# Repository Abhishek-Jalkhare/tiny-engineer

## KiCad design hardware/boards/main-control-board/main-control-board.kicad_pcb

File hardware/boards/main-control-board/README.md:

# main-control-board

This board drives the robot's servos and speaker. Power and USB data come in on a USB-C connector. The Waveshare ESP32-C3-Zero is not soldered down; it plugs into two 9-pin sockets.

- **Status:** draft (schematic and routed layout)
- **KiCad:** 10
- **Built:** not manufactured
- **Tested:** not tested

## Soldered on the board

The servo driver, the speaker amplifier, and the USB-C connector are parts on this PCB. They replace the plug-in PCA9685 board, the MAX98357A breakout, and the Adafruit 5993 USB-C breakout.

- **PCA9685** drives up to 16 PWM channels. This robot uses five of them for the servos. The I2C address is `0x40`: the address pins and the external-clock pin are tied to ground, so the chip uses its own clock.
- **Servo header** takes five servo plugs. Each plug has ground, 5 V, and a PWM signal.
- **MAX98357A** is the mono class-D amplifier. The speaker connects to a 2-pin header. The speaker's minus terminal is not ground. Connect the speaker only between the two amplifier outputs.
- **USB-C connector** supplies 5 V and the USB data pair. Two 5.1 kΩ resistors on the CC pins mark this board as a USB device. The charger decides how much current is available.
- A **3 A resettable fuse** sits between USB power and the 5 V rail.
- A **TPS259571** eFuse (`U4`) sits between that 5 V rail and servo 5 V. Current limit is set by `R14` (1 kΩ ≈ 2 A). On fault the device auto-retries.
- **OLED header** is for the SSD1306 display. Pin order, from pin 1: 3.3 V, ground, SDA, SCL.
- A second header shares that I2C bus. Its pin order is different: ground, 3.3 V, SDA, SCL.
- A **12-pin extension port** (`J4`) breaks out `SERVO_5V`, two grounds, `+3.3V`, I2S BCLK/LRC, and GPIOs GP6–GP9 / GP20 / GP21.
  - GP8 and GP9 are ESP32-C3 strapping pins. Do not pull them low at reset; GP9 low enters download mode.
  - GP20 and GP21 are the default UART0 RX/TX. Boot log output appears on GP21 at power-up.

A solder jumper next to the amplifier is marked as a 6 dB gain limit.

## What still plugs in

The **Waveshare ESP32-C3-Zero** plugs into two 9-pin sockets, one for each row of pins on the module. This board has no ESP32 chip of its own.

The OLED module plugs into the OLED header.

## Power

USB-C 5 V goes through the fuse onto the `+5V` rail. That rail feeds the ESP32 5 V pin, a 5 V indicator LED, and the eFuse input.

The eFuse output is `SERVO_5V`. That rail feeds the servo plugs (PCA9685 V+), a bulk capacitor, and — through a net tie — the amplifier 5 V net, so the amp supply can still be routed on its own but comes from the protected servo rail, not raw `+5V`.

3.3 V comes from the regulator on the ESP32 module. This board does not have a 3.3 V regulator. 3.3 V feeds the PCA9685 logic supply, the OLED, the I2C pull-ups (4.7 kΩ), the pull-up on the PCA9685 output-enable pin (10 kΩ), and a 3.3 V indicator LED.

Servo 5 V and logic 3.3 V stay separate. They share ground.

Use a **5 V supply of at least 2 A**. Five stalled servos can draw more than a typical USB port provides. Multi-servo stall can also hit the eFuse’s ~2 A limit before the 3 A resettable fuse trips.

## Connections from the ESP32

| Function | ESP32 pin | Goes to |
| --- | --- | --- |
| I2C SDA | GP0 | PCA9685 and OLED |
| I2C SCL | GP1 | PCA9685 and OLED |
| I2S bit clock | GP2 | MAX98357A BCLK |
| I2S word clock | GP3 | MAX98357A LRC |
| I2S data | GP4 | MAX98357A DIN |
| Servo output enable | GP5 | PCA9685 output enable (active low) |
| USB D− | GPIO18 | USB-C |
| USB D+ | GPIO19 | USB-C |

GP5 drives PCA9685 OE (`PCA9685_OE_WIRED` in [`include/pins.h`](../../../include/pins.h)). A 10 kΩ pull-up holds OE high until firmware drives it low after neutral park.

## Board

Two-layer FR4, about 1.6 mm thick.

5 V tracks (`+5V` and `SERVO_5V`) are 1.5 mm wide. 3.3 V tracks are 0.4 mm. The amplifier 5 V net is 0.5 mm. USB data tracks use their own width.

The two ESP32 sockets follow the Waveshare header. Pad 1 is 5 V. Pads count anticlockwise from the module's USB connector. Those numbers are the module's header pads, not the pins of the ESP32-C3 chip.

## Library exceptions

### USB1 3D model (C2765186)

Footprint `USB-C-SMD_TYPE-C-16PIN-2MD-073` loads `USB-C-SMD_TYPE-C-6PIN-2MD-073.{wrl,step}`.

EasyEDA has no separate `…16PIN….wrl` for this LCSC part. Official package `c_para.3DModel` is `USB-C-SMD_TYPE-C-6PIN-2MD-073` (outline3D uuid `4ee8413127e64716b804db03d4b340ae`). Re-import via `import_lcsc.py --lcsc-id C2765186` reproduces the same mapping.

Do not rename or replace the model only to silence filename-mismatch reviews — this is intentional.

Contribution rules: [`docs/pcb.md`](../../../docs/pcb.md).

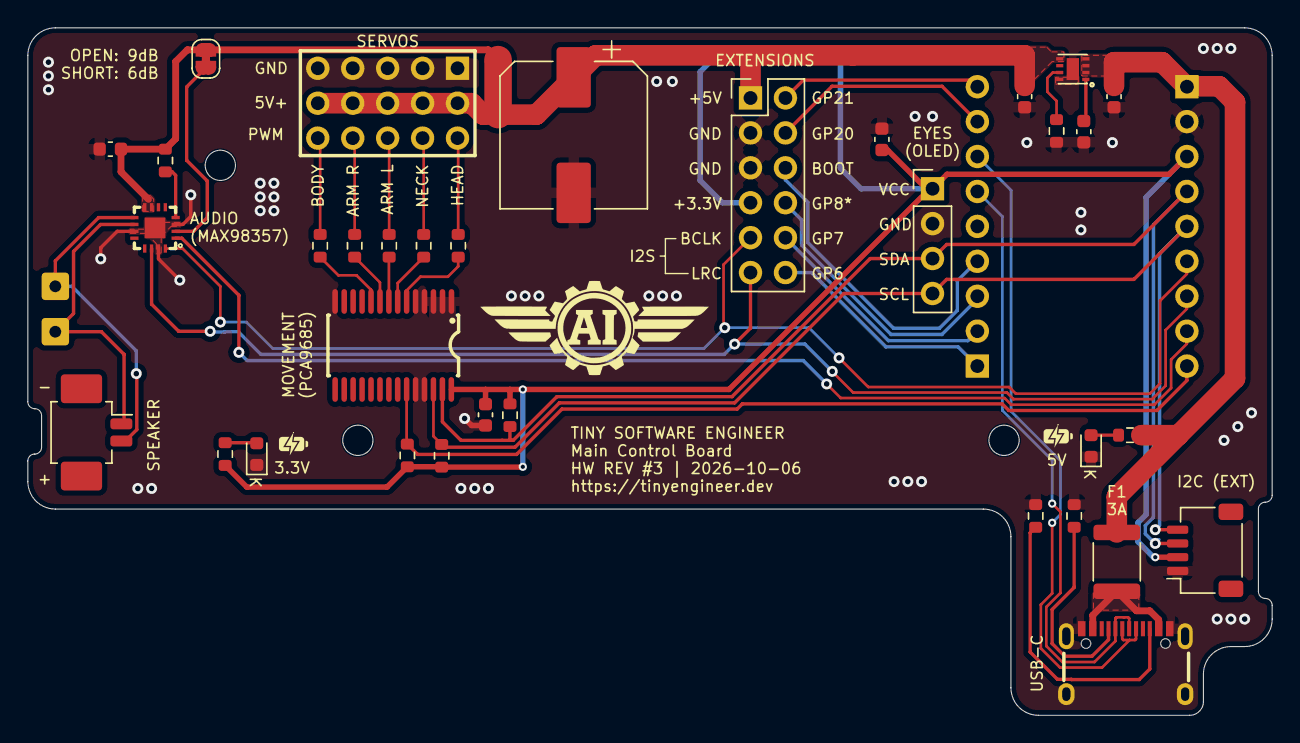
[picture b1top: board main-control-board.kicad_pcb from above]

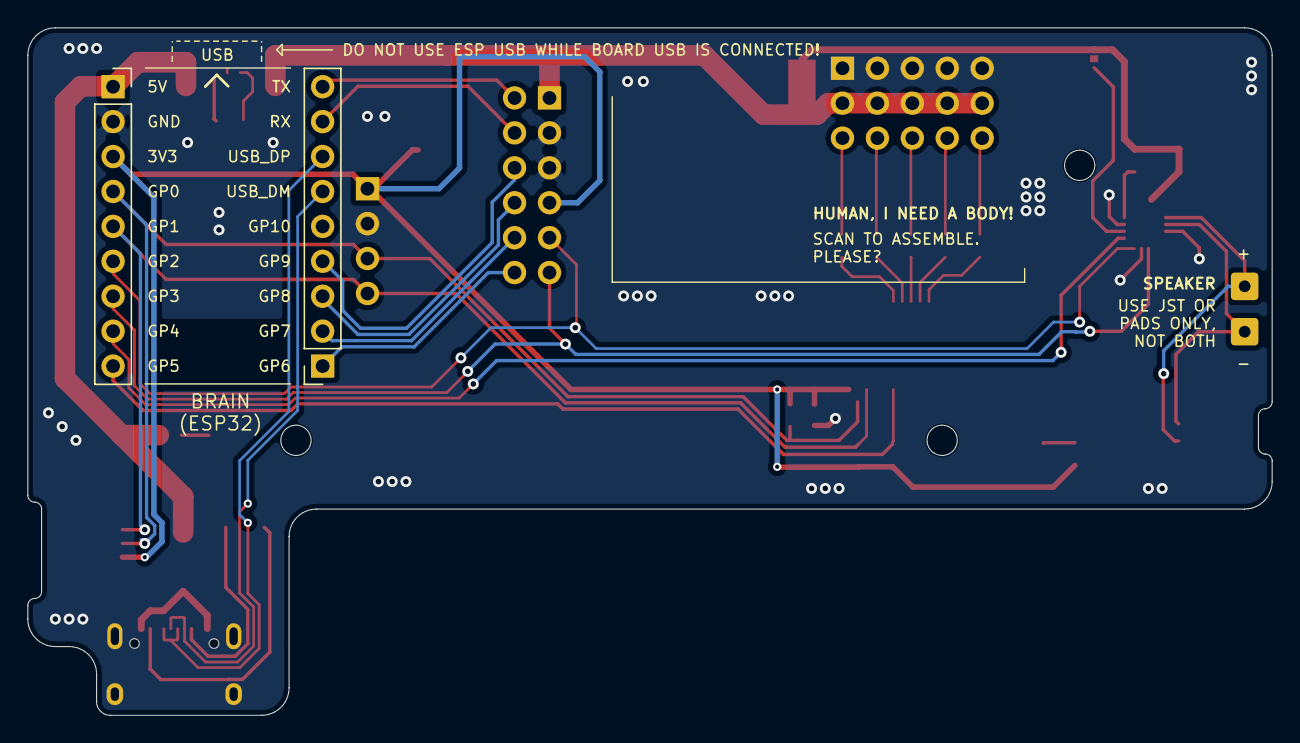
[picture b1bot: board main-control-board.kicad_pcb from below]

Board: 2 copper layers, 90.5 x 50.0 mm, 42 parts (2 on the bottom side), 40 nets.

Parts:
C1, C3, C4, C5, C6, C7: 100nF; C_0603_1608Metric
C2: 1000uF; CP_Elec_10x10.5
D1, D2: LED; LED_0603_1608Metric
F1: 3A PPTC; Fuse_1812_4532Metric
H1, H2, H3: MountingHole; MountingHole_2.2mm_M2
J1: Conn_01x02_Pin_Speaker; Molex_PicoBlade_53261-0271_1x02-1MP_P1.25mm_Horizontal
J2: Conn_OLED; PinHeader_1x04_P2.54mm_Vertical
J3: Conn_extension; JST_SH_SM04B-SRSS-TB_1x04-1MP_P1.00mm_Horizontal
J4: Conn_02x06_Odd_Even; PinHeader_2x06_P2.54mm_Vertical
J7, J8: Conn_ESP32; PinSocket_1x09_P2.54mm_Vertical
JP1: SolderJumper_gain_6dB_limit; SolderJumper-2_P1.3mm_Bridged_RoundedPad1.0x1.5mm
NT1: NetTie_2; NetTie-2_SMD_Pad2.0mm
R1, R2: 5.1k; R_0603_1608Metric
R3: 10k; R_0603_1608Metric
R4, R5: 4.7k; R_0603_1608Metric
R6, R7, R8, R9, R10: 220; R_0603_1608Metric
R11: 2.2k; R_0603_1608Metric
R12: 1M; R_0603_1608Metric
R13, R14: 1k; R_0603_1608Metric
TP1, TP2: TestPoint; SolderWire-0.25sqmm_1x01_D0.65mm_OD2mm
U1: PCA9685PW,118; TSSOP-28_L9.7-W4.4-P0.65-LS6.4-TL
U2: HX PZ2.54-3X5P ZZ; HDR-TH_15P-P2.54-V-M-R3-C5-S7.5
U3: MAX98357AETE+T; TQFN-16_L3.0-W3.0-P0.50-BL-EP1.5
U4: TPS259571DSGR; WSON-8_L2.0-W2.0-P0.50-TL-EP
USB1: TYPE-C 16PIN 2MD; USB-C-SMD_TYPE-C-16PIN-2MD-073

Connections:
+3.3V: C1.2, C7.1, J2.1, J3.2, J4.7, J7.3, R3.1, R4.1, R5.1, R13.1, U1.28 (VDD)
+5V: C4.2, F1.1, J7.1, R11.1, U4.2 (EN/UVLO), U4.3 (IN), U4.4 (IN)
/Audio/AUDIO_5V: C3.2, JP1.1 (A), NT1.2, R12.1, U3.7 (VDD), U3.8 (VDD)
/ESP32/GP5: J7.9, R3.2, U1.23 (~OE)
/ESP32/GP6: J4.12, J8.1
/ESP32/GP7: J4.10, J8.2
/ESP32/GP8: J4.8, J8.3
/ESP32/GP9: J4.6, J8.4
/ESP32/GP20: J4.4, J8.8
/ESP32/GP21: J4.2, J8.9
/I2C_SCL: J2.4, J3.4, J7.5, R4.2, U1.26 (SCL)
/I2C_SDA: J2.3, J3.3, J7.4, R5.2, U1.27 (SDA)
/I2S_BCLK: J4.9, J7.6, U3.16 (BCLK)
/I2S_DIN: J7.8, U3.1 (DIN)
/I2S_LRC: J4.11, J7.7, U3.14 (LRCLK)
/PCA/SERVO_5V: C2.1, C5.2, J4.1, NT1.1, U2.2, U2.5, U2.8, U2.11, U2.14, U4.5 (OUT)
/USB/USB_VBUS: F1.2, USB1.A4B9 (VBUS), USB1.B4A9 (VBUS)
/USB_D+: J8.7, USB1.A6 (Dp1), USB1.B6 (Dp2)
/USB_D-: J8.6, USB1.A7 (Dn1), USB1.B7 (Dn2)
GND: C1.1, C2.2, C3.1, C4.1, C5.1, C6.2, C7.2, D1.1 (K), D2.1 (K), J2.2, J3.1, J4.3, J4.5, J7.2, R1.1, R2.1, R14.2, U1.1 (A0), U1.2 (A1), U1.3 (A2), U1.4 (A3), U1.5 (A4), U1.14 (VSS), U1.24 (A5), U1.25 (EXTCLK), U2.1, U2.4, U2.7, U2.10, U2.13, U3.3 (GND), U3.11 (GND), U3.15 (GND), U3.17 (EP), U4.8 (GND), U4.9 (GND), USB1.13 (EH), USB1.14 (EH), USB1.A1B12 (GND), USB1.B1A12 (GND)
unnamed: D1.2 (A), R11.2
unnamed: D2.2 (A), R13.2
unnamed: J1.1, TP1.1 (1_1), U3.10 (OUTN)
unnamed: J1.2, TP2.1 (1_1), U3.9 (OUTP)
unnamed: JP1.2 (B), U3.2 (GAIN_SLOT)
unnamed: R6.2, U2.3
unnamed: R7.2, U2.6
unnamed: R8.2, U2.9
unnamed: R9.2, U2.12
unnamed: R10.2, U2.15
unnamed: R6.1, U1.6 (LED0)
unnamed: R7.1, U1.7 (LED1)
unnamed: R8.1, U1.8 (LED2)
unnamed: R9.1, U1.9 (LED3)
unnamed: R10.1, U1.10 (LED4)
unnamed: R12.2, U3.4 (~SD_MODE)
unnamed: R14.1, U4.7 (ILM)
unnamed: C6.1, U4.1 (dVdt)
unnamed: R1.2, USB1.A5 (CC1)
unnamed: R2.2, USB1.B5 (CC2)
